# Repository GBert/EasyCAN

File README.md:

Easy and cheap CAN interface
============================

This repo contains a project of a CAN interface. Main goals are:
- should be cheap
- one layer for homemade PCB or PCB manufacturing in 5cm\*5cm design
- flexible (galvanic isolated is an option)
- useable by many programs and OS (SLCAN API)
- no PIC programmer needed

Price target is 15$ - depends on galvanic isolation 

### Firmware

Bootloader ([Wellington](http://hg.kewl.org/pub/wellington/)) is programmed by the cheap CP2102 board with Darron Broads [k8048](http://dev.kewl.org/k8048/Doc/). The firmware itself is programmed by the bootloader. So no PIC programmer needed.

### Status

- working test PCB
- working Wellington bootloader
- working easy-loader from Darron Broad
- first working SLCAN firmware (thx to Darron Broad for his excellent work)
- needs slcand\_rts if jumper remains

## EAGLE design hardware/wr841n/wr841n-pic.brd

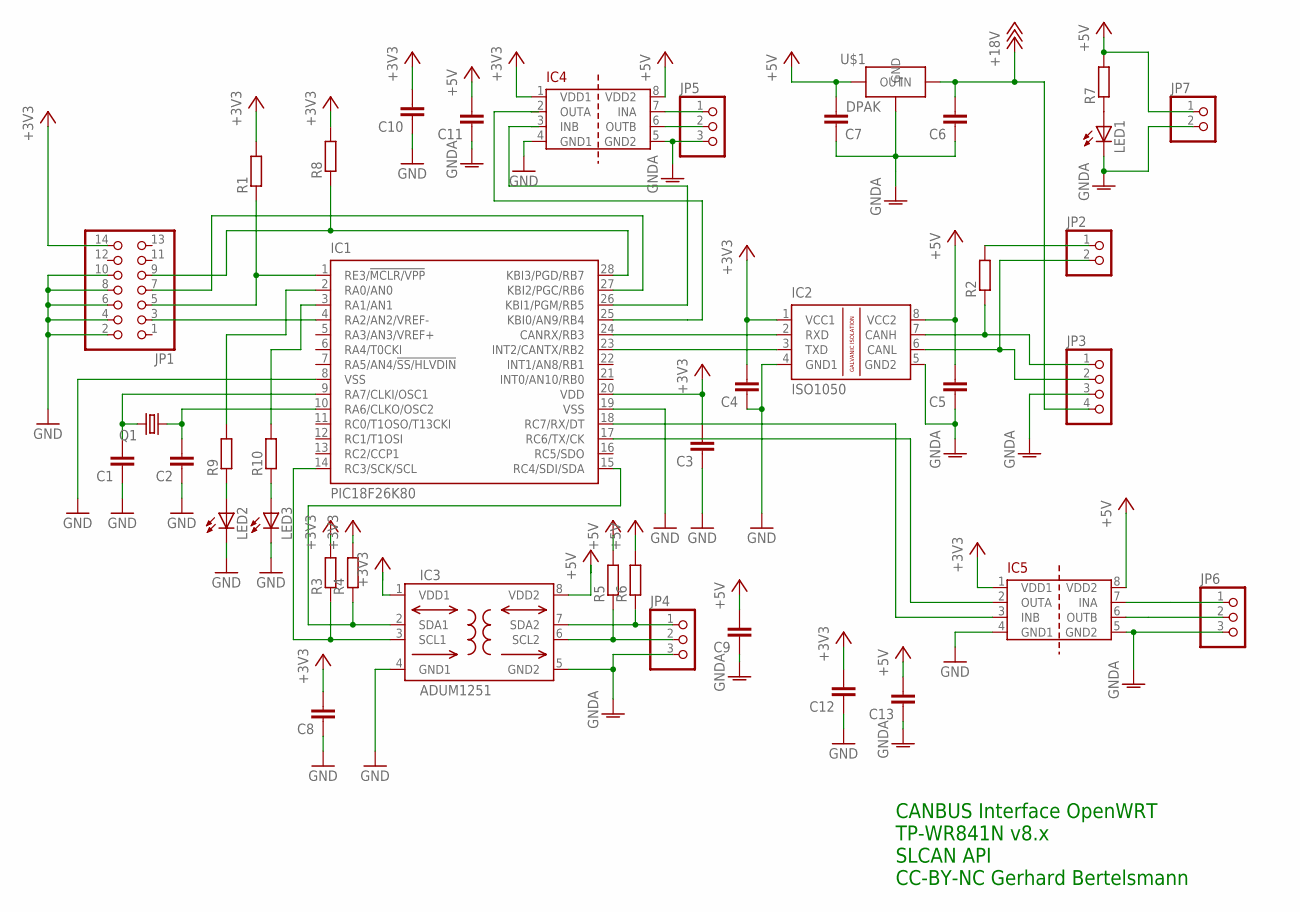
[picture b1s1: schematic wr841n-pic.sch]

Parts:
C1, C2, C3, C4, C5, C6, C7, C8, C9, C10, C11, C12, C13: C-EUC1206; C1206
IC1: PIC18F26K80; SO28W
IC2: ISO1050; DUB-R-PDSO-G8
IC3: ADUM1251; SO8-COOL
IC4, IC5: ADUM1201; SO8
JP1: PINHD-2X7; 2X07
JP2, JP7: PINHD-1X2; 1X02
JP3: PINHD-1X4; 1X04
JP4, JP5, JP6: PINHD-1X3; 1X03
LED1, LED2, LED3: LEDCHIPLED_1206; CHIPLED_1206
Q1: CRYSTALHC49UP; HC49UP
R1, R2, R3, R4, R5, R6, R7, R8, R9, R10: R-EU_R1206; R1206
U$1: 7805-DPAK

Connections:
+3V3: C3.2, C4.2, C8.2, C10.2, C12.2, IC1.20 (VDD), IC2.1 (VCC1), IC3.1 (VDD1), IC4.1 (VDD1), IC5.1 (VDD1), JP1.14, R1.2, R3.2, R4.2, R8.2
+5V: C5.2, C7.2, C9.2, C11.2, C13.2, IC2.8 (VCC2), IC3.8 (VDD2), IC4.8 (VDD2), IC5.8 (VDD2), JP7.1, R5.2, R6.2, R7.2, U$1.OUT; also elsewhere on the board
+18V: C6.2, JP3.4, U$1.IN; also elsewhere on the board
GND: C1.1, C2.1, C3.1, C4.1, C8.1, C10.1, C12.1, IC1.8 (VSS), IC1.19 (VSS), IC2.4 (GND1), IC3.4 (GND1), IC4.4 (GND1), IC5.4 (GND1), JP1.2, JP1.4, JP1.6, JP1.8, JP1.10, LED2.C, LED3.C
GNDA: C5.1, C6.1, C7.1, C9.1, C11.1, C13.1, IC2.5 (GND2), IC3.5 (GND2), IC4.5 (GND2), IC5.5 (GND2), JP3.3, JP4.3, JP5.3, JP6.3, JP7.2, LED1.C, U$1.GND; also elsewhere on the board
unnamed: C1.2, IC1.9 (RA7/CLKI/OSC1), Q1.2
unnamed: C2.2, IC1.10 (RA6/CLKO/OSC2), Q1.1
unnamed: IC1.1 (RE3/!MCLR/VPP), JP1.5, R1.1
unnamed: IC1.28 (KBI3/PGD/RB7), JP1.9, R8.1
unnamed: IC1.27 (KBI2/PGC/RB6), JP1.7
unnamed: IC1.24 (CANRX/RB3), IC2.2 (RXD)
unnamed: IC1.23 (INT2/CANTX/RB2), IC2.3 (TXD)
unnamed: IC2.7 (CANH), JP3.1, R2.1
unnamed: JP2.1, R2.2
unnamed: IC2.6 (CANL), JP2.2, JP3.2
unnamed: IC3.7 (SDA2), JP4.1, R6.1
unnamed: IC3.6 (SCL2), JP4.2, R5.1
unnamed: IC1.14 (RC3/SCK/SCL), IC3.3 (SCL1), R3.1
unnamed: IC1.15 (RC4/SDI/SDA), IC3.2 (SDA1), R4.1
unnamed: LED1.A, R7.1
unnamed: IC1.3 (RA1/AN1), R10.2
unnamed: IC4.7 (INA), JP5.1
unnamed: IC4.6 (OUTB), JP5.2
unnamed: IC1.17 (RC6/TX/CK), IC5.2 (OUTA)
unnamed: IC5.7 (INA), JP6.1
unnamed: IC5.6 (OUTB), JP6.2
unnamed: IC1.18 (RC7/RX/DT), IC5.3 (INB)
unnamed: IC1.4 (RA2/AN2/VREF-), JP1.3
unnamed: IC1.26 (KBI1/PGM/RB5), IC4.3 (INB)
unnamed: IC1.25 (KBI0/AN9/RB4), IC4.2 (OUTA)
unnamed: IC1.2 (RA0/AN0), R9.2
unnamed: LED2.A, R9.1
unnamed: LED3.A, R10.1

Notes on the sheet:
CANBUS Interface OpenWRT TP-WR841N v8.x SLCAN API CC-BY-NC Gerhard Bertelsmann

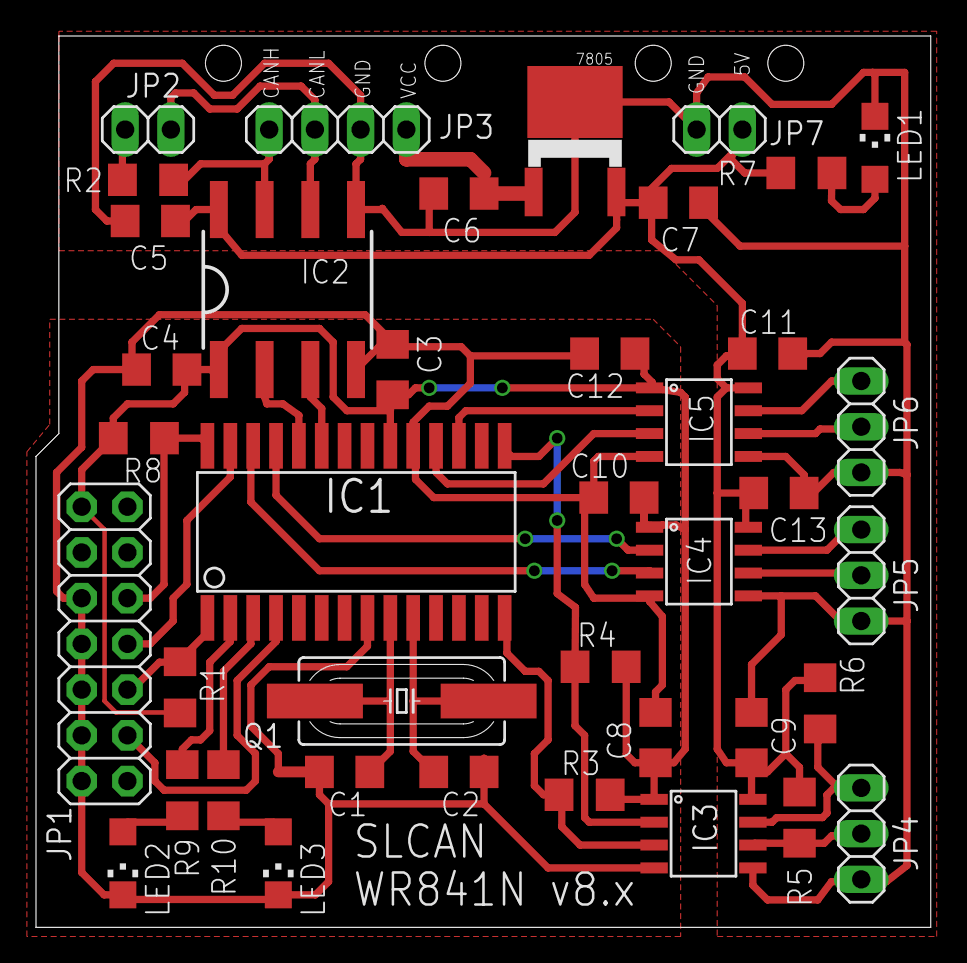
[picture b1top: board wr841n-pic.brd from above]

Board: 2 copper layers, 49.7 x 49.5 mm, 40 parts (0 on the bottom side), 33 nets.

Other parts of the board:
7805: 7805-DPAK

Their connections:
+5V: 7805.OUT; also elsewhere on the board
+18V: 7805.IN; also elsewhere on the board
GNDA: 7805.GND; also elsewhere on the board

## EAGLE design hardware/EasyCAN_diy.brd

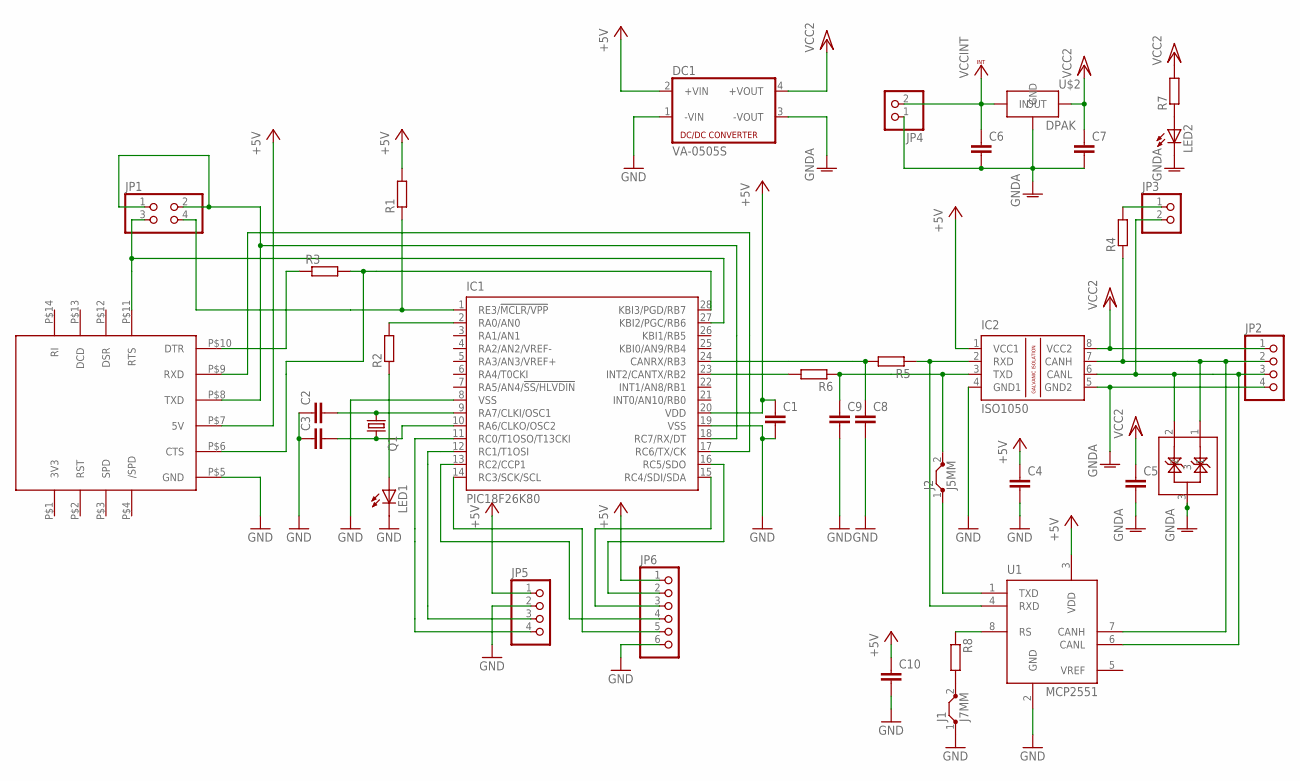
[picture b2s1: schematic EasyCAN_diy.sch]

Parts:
C1, C2, C3, C4, C5, C6, C7, C8, C9, C10: C-EUC1206; C1206
D1: NUP2105L; TO236
DC1: VA-0505S; 4SIL
IC1: PIC18F26K80; SO28W
IC2: ISO1050; DUB-R-PDSO-G8
J1: J7MM; 07
J2: J5MM; 05
JP1: PINHD-2X2; 2X02
JP2, JP5: PINHD-1X4; 1X04
JP3, JP4: PINHD-1X2; 1X02
JP6: PINHD-1X6; 1X06
LED1, LED2: LEDSML1206; SML1206
Q1: CRYSTALHC49UP; HC49UP
R1, R2, R3, R5, R6, R7, R8: R-EU_R1206; R1206
R4: R-EU_0204/7; 0204/7
U1: MCP2551; SO-08
U$1: BTE13-007
U$2: 7805-DPAK

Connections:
3V3: U$1.P$1 (3V3)
+5V: C1.1, C4.1, C10.1, DC1.2 (+VIN), IC1.20 (VDD), IC2.1 (VCC1), JP5.1, JP6.1, R1.2, U1.3 (VDD), U$1.P$7 (5V)
GND: C1.2, C2.1, C3.1, C4.2, C8.2, C9.2, C10.2, DC1.1 (-VIN), IC1.8 (VSS), IC1.19 (VSS), IC2.4 (GND1), J1.1, JP5.2, JP6.6, LED1.C, U1.2 (GND), U$1.P$5 (GND)
GNDA: C5.2, C6.2, C7.2, D1.3, DC1.3 (-VOUT), IC2.5 (GND2), JP2.4, JP4.1, LED2.C, U$2.GND
unnamed: IC1.18 (RC7/RX/DT), JP1.1, JP1.2, U$1.P$8 (TXD)
unnamed: IC1.17 (RC6/TX/CK), U$1.P$9 (RXD)
unnamed: C2.2, IC1.9 (RA7/CLKI/OSC1), Q1.2
unnamed: C3.2, IC1.10 (RA6/CLKO/OSC2), Q1.1
unnamed: IC1.2 (RA0/AN0), R2.2
unnamed: IC1.1 (RE3/!MCLR/VPP), JP1.4, R1.1
unnamed: IC1.27 (KBI2/PGC/RB6), JP1.3, U$1.P$11 (RTS)
unnamed: IC2.2 (RXD), R5.1, U1.4 (RXD)
unnamed: IC1.28 (KBI3/PGD/RB7), R3.2, U$1.P$6 (CTS)
unnamed: R3.1, U$1.P$10 (DTR)
unnamed: C8.1, IC1.24 (CANRX/RB3), R5.2
unnamed: J1.2, R8.2
unnamed: LED2.A, R7.1
unnamed: R8.1, U1.8 (RS)
unnamed: C9.1, IC2.3 (TXD), J2.2, R6.1
unnamed: JP3.1, R4.2
unnamed: LED1.A, R2.1
unnamed: IC1.11 (RC0/T1OSO/T13CKI), JP5.4
unnamed: IC1.12 (RC1/T1OSI), JP5.3
unnamed: IC1.13 (RC2/CCP1), JP6.4
unnamed: IC1.14 (RC3/SCK/SCL), JP6.5
unnamed: IC1.15 (RC4/SDI/SDA), JP6.3
unnamed: IC1.16 (RC5/SDO), JP6.2
unnamed: D1.2, IC2.6 (CANL), JP2.3, JP3.2, U1.6 (CANL)
unnamed: D1.1, IC2.7 (CANH), JP2.2, R4.1, U1.7 (CANH)
unnamed: IC1.23 (INT2/CANTX/RB2), R6.2
unnamed: J2.1, U1.1 (TXD)
VCC/2: C5.1, C7.1, DC1.4 (+VOUT), IC2.8 (VCC2), JP2.1, R7.2, U$2.OUT
VCCINT: C6.1, JP4.2, U$2.IN

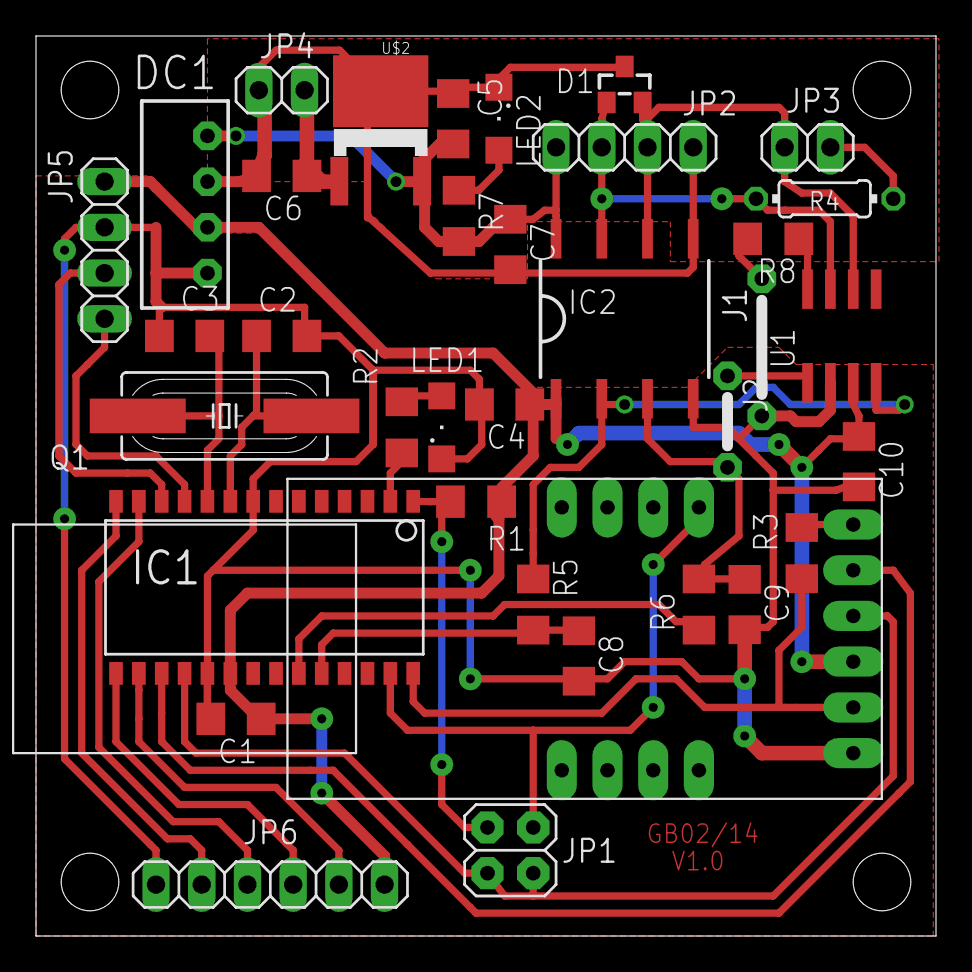
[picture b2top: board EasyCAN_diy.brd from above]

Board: 2 copper layers, 50.0 x 50.0 mm, 36 parts (0 on the bottom side), 32 nets.

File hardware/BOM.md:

BOM
===

```
R1		4k7
R2,R7		330  (20mA LED)
R4		120
R5,R6		33
R8		1k	optional (MCP2551 bzw. 2561)

C1		100nF
C2,C3		22pF
C4-C7		100nF
C8,C9		100pF
C10		100nF	optional 

IC1		PIC18F25K80 oder PIC18F26K80
Q1		16MHz

DC1		5V DCDC SIL4	optional
		NUP2105L        CAN protection optional 
```

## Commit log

2014-02-10 add Eagle files for DIY
2014-02-10 TinyBLD - wip
2014-02-10 TinyBLD - reorganize
2014-02-10 add some notes to README
2014-02-10 cleanup and try to fix config regs
2014-02-10 add HEX file
2014-02-11 try to fix uart init
2014-02-13 grrrr - wip
2014-02-17 add tinybld cli from Joseph Heenan - wip
2014-02-17 tinybld on 18f26k80 working - cli wip
2014-02-17 cli: add some pic ids and fix debug print
2014-02-17 fix pci ids in asm file
2014-02-17 use options
2014-02-17 clarify RTS signal
2014-02-17 fix RTS handling - part I
2014-02-17 fix RTS handling - part II
2014-02-18 try ds30loader
2014-02-18 changed CONFIG entries similar to working tinybld
2014-02-18 changed to 115200 baud
2014-02-18 try to adapt Bus Pirate ds30client
2014-02-18 add usbreset.c
2014-02-19 add RTS handling
2014-02-19 minimalistic desc
2014-02-20 stretch RTS / PIC reset
2014-03-05 bug hunting
2014-03-05 xc8 testing
2014-03-05 add files from bt-relay
2014-03-05 uart test
2014-03-05 uart test - wip part XIV
2014-03-06 fix termios settings (why ? i don't know)
2014-04-25 try the pirate loader - changed PIC to PIC18F26K80
2014-06-24 first working version - very dirty hack
2014-06-25 writing data works. but GOTO bootloader is missing - still dirty hack
2014-06-25 add LST from ds30loader -> fix jumps
2014-06-25 switch back to word size - try to fix 'fix jump'
2014-06-25 try to fix 'fix jump' wip
2014-06-25 wip - fix word handling
2014-06-25 fix PIC WORD SIZE
2014-06-26 fixed jumps - hopefully
2014-06-26 fix jumps - again
2014-06-26 fix jumps - again and again
2014-06-26 jalv2 -long-start generated blinky
2014-06-27 first working version - reduce some printfs
2014-06-28 add schematic pdf
2014-06-30 what we all need is blinky
2014-06-30 notes added
2014-06-30 noteas add - part II
2014-06-30 try timer0 interrupt
2014-06-30 be more accurate
2014-06-30 collect examples
2014-06-30 add more (e)can examples
2014-06-30 stir well - and done ;-)
2014-06-30 IRQ blinky as hearbeat
2014-06-30 palying with ISR
2014-07-01 start writing the ultimate code ...
2014-07-02 add test for UART fifo
2014-07-02 trying cricual serial buffers
2014-07-02 fix circular buffer handling - change return values
2014-07-02 change return value
2014-07-02 change usart ready check
2014-07-02 add little tool to set rts
2014-07-02 play with USART init
2014-07-02 test simple circular
2014-07-03 add some random jalv2 stuff
2014-07-03 still fighting with USART init
2014-07-03 add simple terminal programm
2014-07-03 add RTS settings
2014-07-03 fifo print out of order - try a single char
2014-07-03 fixed sending char - yahooooo
2014-07-03 do some USART function tests
2014-07-03 play with strings
2014-07-03 play with strings in flash
2014-07-03 play with strings in flash - part II
2014-07-03 could compile on linux
2014-07-03 fix hex print
2014-07-04 USART working - work on fifo. USART needs special RTS handling ...
2014-07-04 fighting against fifo
2014-07-05 add sdcc test
2014-07-06 famous blinky with sdcc - fails on ds30loader
2014-07-06 fixed blinky !
2014-07-06 fixed comments
2014-07-07 trail and error
2014-07-07 Makefile for jal
2014-07-07 prepare CAN bit timing - add/fix Makefile
2014-07-07 fix Makefile
2014-07-07 add vV switch SLCAN
2014-07-07 tyr mplab output
2014-07-08 disable XINST and WDT
2014-07-08 fix typo in readme
2014-07-09 after fixing dsloader (XINST and WDT off) try some code
2014-07-09 circular buffer is working
2014-07-10 reorganize firmware
2014-07-10 ignore alligment for config registers
2014-07-10 get rid off XINST pragma message
2014-07-11 add receiver - wip
2014-07-11 fix receiver fifo wrap around
2014-07-11 add copy fifo function
2014-07-11 add putchar_fifo
2014-07-11 tidy up
2014-07-17 start with CAN fun
2014-07-17 sfr print fun - wip
2014-07-17 can wip
2014-07-17 use more CAN functions
2014-07-17 more fun with can
2014-07-20 work on CAN init code
2014-07-21 add CAN port assignement
2014-07-24 add CAN functions - wip
2014-07-24 change mask to accept all CAN frames and add some debugging
2014-07-25 get rid off some BANKSELs
2014-07-25 change CAN register settings - unroll loops - use glbal vars. Trying to make the code smaller&faster + easier to read
2014-07-25 try to get first CAN message
2014-07-27 first attemp to send CAN frame. Works, but BRGCONxs are still wrong ...
2014-07-27 fix CAN timimg values
2014-07-28 try to find out why extended CAN frames are blocked
2014-07-28 fix extended CAN frame filter&mask
2014-07-28 set buffer to accept all CAN messages
2014-07-28 decode RX CAN frame -> SLCAN - wip
2014-07-30 fix CAN Id claculation
2014-07-31 enable rollover RXB0 to RXB1 if necessary
2014-08-02 note that port.de is correct
2014-08-04 disable analog completely
2014-08-04 try JAl version
2014-10-05 add pictures
2014-10-05 add thumbs
2014-10-05 add thumbs - ?
2014-10-05 rearrange pictures
2014-10-05 fix thumb
2014-11-03 use the cleaner Darron Broads Easy Loader
2014-11-06 reorganize
2014-11-06 use the clean Wellington bootloader
2014-11-06 change bootlader in doc
2014-11-06 fix typo
2014-11-06 readme house keeping
2014-11-06 fix link
2014-11-06 house keeping
2014-11-06 move old files
2014-11-06 add quiet mode for easy-loader
2014-11-14 do can_rx conversion - wip
2014-11-15 change to wellington bootloader tool
2014-11-15 make the crstal work ...
2014-11-15 add trial Makefile switch for fast trial&error
2014-11-16 use Darrons updates on com and easy-loader
2014-11-16 set default baudrate to 500k
2014-11-16 new easy-loader - less buggy as Darron said ...
2014-11-16 some updates for CAN
2014-11-17 try Darron's approach
2014-11-17 add some testing targets to makefile and fix CAN baud settings
2014-11-17 disable 9 bit USART (2 stop bits)
2014-11-17 add can-can test
2014-11-17 change USB tty
2014-11-17 switch all ports to digital
2014-11-17 reduce redundant port settings
2014-11-17 can-can still not working here ...
2014-11-17 make can-can work; add some easy-can TX tranmit optimization in advance
2014-11-17 test @125k CAN
2014-11-17 use latest can-can test code
2014-11-18 testing now with 250k CAN 500k TTY
2014-11-18 add 2 stop bits option
2014-11-18 fix include define
2014-11-18 use Darrons latest and greatest can-can
2014-11-18 set XSTA to the first UART
2014-11-19 uart tweaking - now 250k TX CAN ready !
2014-11-19 tweak UART settings
2014-11-20 add 500k CAN settings
2014-11-20 add some generic UART defines
2014-11-20 use new can-can testing tool
2014-11-20 add old version - backup
2014-11-20 rename TX_FLUSH and minimize calling it
2014-11-20 prepare RX buffer
2014-11-21 new stage
2014-11-21 setup WIP
2014-11-21 setup ports - but no go ...
2014-11-21 strike - Hello World!
2014-11-22 add fast ASCI<->HEX conversion routines
2014-11-22 new ISR - speed upgrade
2014-11-24 jump onto next version
2014-11-24 add CAN baud rates
2014-11-24 set baudrate to 460800
2014-11-24 use new test code - wip
2014-11-24 new version test
2014-11-25 use new code from Darron
2014-11-25 holy microchip shit - aka as TXIF madness
2014-11-25 add new incs
2014-11-26 use new version add fix CAN startup
2014-11-26 honor the master ...
2014-11-26 next try - tidy fifos
2014-11-26 sending txreg
2014-11-28 follow Darrons Code
2014-11-28 extended CANID rotines and fixes
2014-11-28 add scripts and special slcand for EasyCAN
2014-11-28 yes - we do have the first working version
2014-11-28 add bouncing test
2014-11-29 prepare fixing rx overload
2014-11-29 fix CANRX overflow - simply drop it
2014-11-29 fix flow control
2014-11-29 tidy git
2014-11-29 add Darrons firmware
2014-11-30 LED modify
2014-11-30 prepare file for WR841N v8.x CAN interface
2014-12-01 reflect files we need
2014-12-01 rename file to get make happy
2014-12-01 need to integrate init
2014-12-01 add init ports
2014-12-01 add config register settings for non bootloader
2014-12-01 add previously deleted bootloader files
2014-12-01 add blinky again
2014-12-01 using 16MHz XTAL with 4xPLL
2014-12-02 use next version
2014-12-02 remove subversion file
2014-12-02 remove object file
2014-12-03 use new CTS/RTS mechanism
2014-12-05 fix polarity
2014-12-05 add WR841 temporarily
2014-12-07 CAN-CAN WR841N PCB wip
2014-12-08 finalize PCB -> manufactor
2014-12-08 add license
2014-12-09 change IC1 outline
2014-12-09 reflect changes in Gerber files
2015-09-07 add DIY Gleisbox CAN Interface
2016-07-05 add BOM
2016-07-05 fix BOM
2017-10-24 update schematic
